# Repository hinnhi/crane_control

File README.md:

# Crane Control

 :building_construction: The following circuit has the purpose of managing three engines controlled by a web app also used as a safety system, 
since upon activation of one of the available motors, If the crane is performing a previously selected operation, 
the operation stops allowing the new selected movement to start. Within the site there are several selectable boxes, such as:
- "Motor 1"; which is associated with the movement of the crane shaft, allowing the rotation to the right or left.
- "Motor 2";  to which is associated the sliding (forward-backward) of the basket along the axis.
- "Motor 3";  which is associated with the climb-down of the basket.
- "Reset"; used to reset the crane axles.

The esp32 connects to a wifi network of which must be provided SSID & PASSWORD and sets the status of the web app to the state "Idle".
Next, if connected to wifi, send requests to the web app and upload the data received in the variable "payload". 
```
int httpCode = http.GET();
if (httpCode > 0){
      payload = http.getString();
      intpayload = payload.toInt();
}
```
The data that can be received, integer type,  can be:
- "1" if Motor 1 has been selected (clockwise spinning)
- "2" if Motor 1 has been selected (counter clockwise spinning)
- "3" if Motor 2 has been selected (clockwise spinning)
- "4" if Motor 2 has been selected (counter clockwise spinning)
- "5" if Motor 3 has been selected (clockwise spinning)
- "6" if Motor 3 has been selected (counter clockwise spinning)
- "7" if selected Reset
  
Depending on the data received, the program will operate the corresponding motor in the corresponding direction.

## Central circuit :space_invader:
[The following circuit](https://github.com/hinnhi/crane_control/tree/main/circuit/circuito_centrale) is responsible for controlling the 3 crane engines. If the relay is not powered 
(so the bistable button, which takes care of stopping all the motors in case of failure/ emergency, has not been pressed) 
the two h bridges are powered by the VCC supply voltage. Once the data is received by the web app, the esp32 sends a 3.3V 
signal output, the signal is sent to a photocoupler and successively to the inputs of the bridge h. The photocouplers are 
used to separate the control part (powered at 3.3V) and that of power (powered by 5V).

## Acoustic and light warning circuit
[The following circuit](https://github.com/hinnhi/crane_control/tree/main/circuit/segnalazione_acustico_luminosa) deals with the acoustic and light signaling of the crane, the LED and the buzzer are operated thanks 
to the use of the integrated circuit [NE555](https://en.wikipedia.org/wiki/555_timer_IC) as a square wave generator. If the relay is powered (so the bistable button, which takes 
care of stopping all the motors in case of failure/ emergency, has been pressed), the integrated NE555 is powered by the VCC 
supply voltage. The circuit also takes care of receiving the VCC supply voltage from the generator and "distribute" it to the 
other circuits, "host" the connectors that connect the limit switches to the espe32 and the bistable button that activates the 
relay. 

## LED blinking circuit
[The following circuit](https://github.com/hinnhi/crane_control/tree/main/circuit/lampeggio_led), realized on millephous base, deals with the light signaling of the crane. The LED flashes thanks to the 
use of the integrated circuit NE555 as a square wave generator. The capacitor C3 is charged with the supply voltage VCC=5V, through the 
two resistors RA and RB; as soon as the power on the capacitor exceeds the level 2/3VCC, the comparator A passes the output Q of the 
flip-flop from low to high, as a result, the T1 transistor goes into saturation and the C3 capacitor begins to discharge through 
the RB resistor. The discharge proceeds until the charge on the capacitor C3 becomes less than 1/3VCC; at this point the comparator 
B makes again change state on the flip-flop bringing the output Q to the low level and the cycle starts again.

Wave period square output:  T = Tc + Ts = (RA+2RB)C3ln(2)

> [!NOTE]
> The power supply voltage can be raised up to 40 volts, but the interfaces for the acoustic and light warning circuit and for the LED blinking circuit must be redesigned.

> [!WARNING]
> Neutral wires of esp32 and power supply must not be connected together.

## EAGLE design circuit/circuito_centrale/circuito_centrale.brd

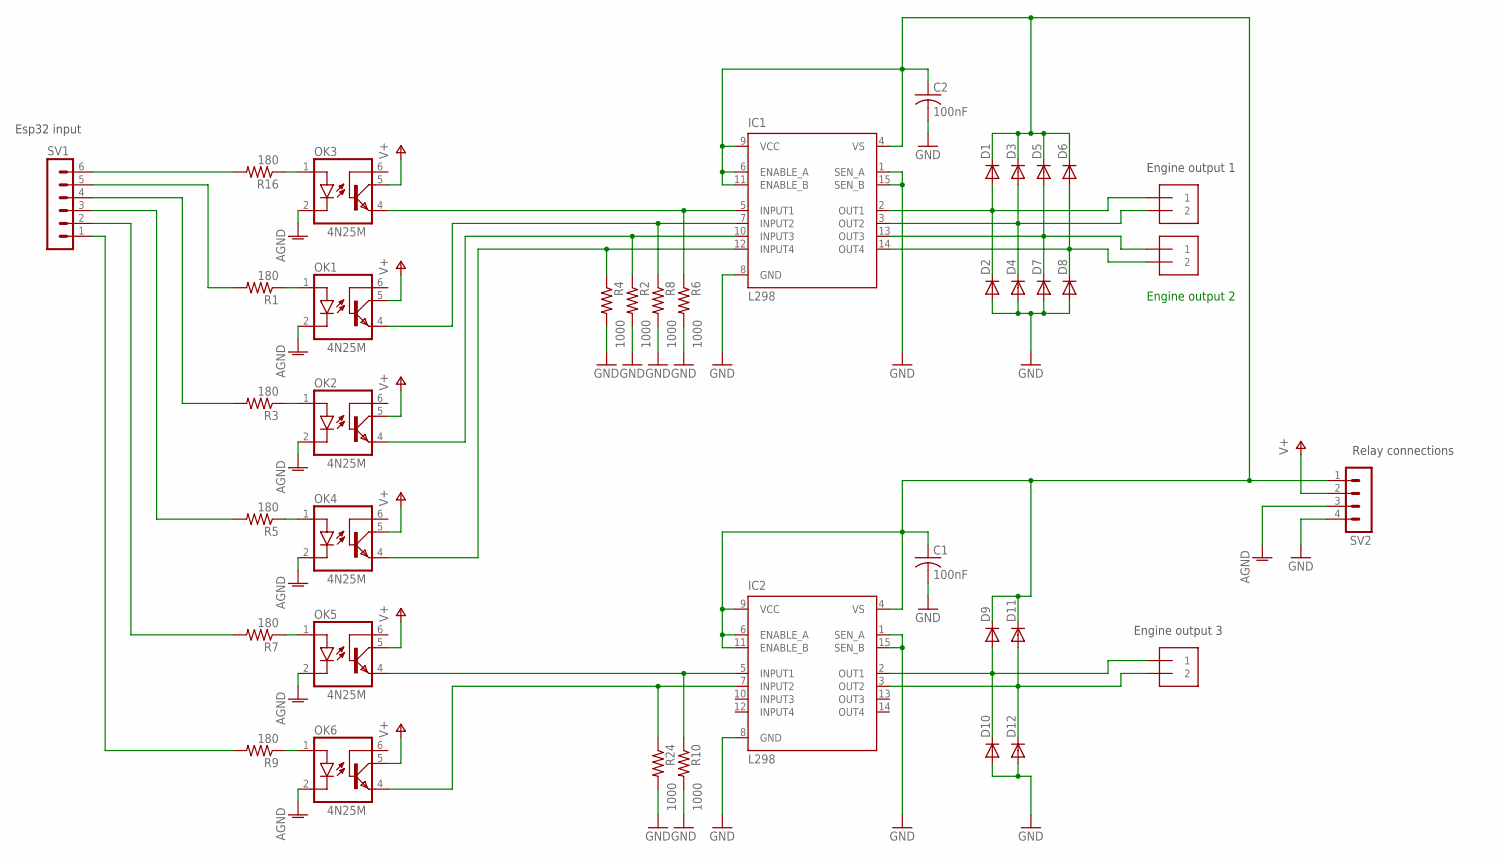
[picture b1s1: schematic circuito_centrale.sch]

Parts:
C1, C2: 100nF; C050-024X044
D1, D2, D3, D4, D5, D6, D7, D8, D9, D10, D11, D12: DIODE-D-5; D-5
IC1, IC2: L298; MULTIWATT-15
J2, J3, J5: 1X2-3.5MM
OK1, OK2, OK3, OK4, OK5, OK6: 4N25M; DIL06
R1, R3, R5, R7, R9, R16: 180; 0207/10
R2, R4, R6, R8, R10, R24: 1000; 0207/10
SV1: MA06-1
SV2: MA04-1

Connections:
AGND: OK1.2 (C), OK2.2 (C), OK3.2 (C), OK4.2 (C), OK5.2 (C), OK6.2 (C), SV2.3
GND: C1.2, C2.2, D2.A, D4.A, D7.A, D8.A, D10.A, D12.A, IC1.1 (SEN_A), IC1.8 (GND), IC1.15 (SEN_B), IC2.1 (SEN_A), IC2.8 (GND), IC2.15 (SEN_B), R2.2, R4.2, R6.2, R8.2, R10.2, R24.2, SV2.4
unnamed: D1.A, D2.C, IC1.2 (OUT1), J2.1
unnamed: D3.A, D4.C, IC1.3 (OUT2), J2.2
unnamed: D6.A, D8.C, IC1.14 (OUT4), J3.2
unnamed: D5.A, D7.C, IC1.13 (OUT3), J3.1
unnamed: IC1.5 (INPUT1), OK3.4 (EMI), R6.1
unnamed: OK1.1 (A), R1.1
unnamed: R1.2, SV1.5
unnamed: IC1.7 (INPUT2), OK1.4 (EMI), R8.1
unnamed: IC1.10 (INPUT3), OK2.4 (EMI), R2.1
unnamed: OK2.1 (A), R3.1
unnamed: R3.2, SV1.4
unnamed: IC1.12 (INPUT4), OK4.4 (EMI), R4.1
unnamed: IC2.5 (INPUT1), OK5.4 (EMI), R10.1
unnamed: OK4.1 (A), R5.1
unnamed: R5.2, SV1.3
unnamed: IC2.7 (INPUT2), OK6.4 (EMI), R24.1
unnamed: D9.A, D10.C, IC2.2 (OUT1), J5.1
unnamed: D11.A, D12.C, IC2.3 (OUT2), J5.2
unnamed: R7.2, SV1.2
unnamed: OK3.1 (A), R16.1
unnamed: R16.2, SV1.6
unnamed: R9.2, SV1.1
unnamed: OK5.1 (A), R7.1
unnamed: OK6.1 (A), R9.1
unnamed: C1.1, C2.1, D1.C, D3.C, D5.C, D6.C, D9.C, D11.C, IC1.4 (VS), IC1.6 (ENABLE_A), IC1.9 (VCC), IC1.11 (ENABLE_B), IC2.4 (VS), IC2.6 (ENABLE_A), IC2.9 (VCC), IC2.11 (ENABLE_B), SV2.1
V+: OK1.5 (COL), OK2.5 (COL), OK3.5 (COL), OK4.5 (COL), OK5.5 (COL), OK6.5 (COL), SV2.2

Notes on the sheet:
Esp32 input
Engine output 1
Engine output 2
Engine output 3
Relay connections

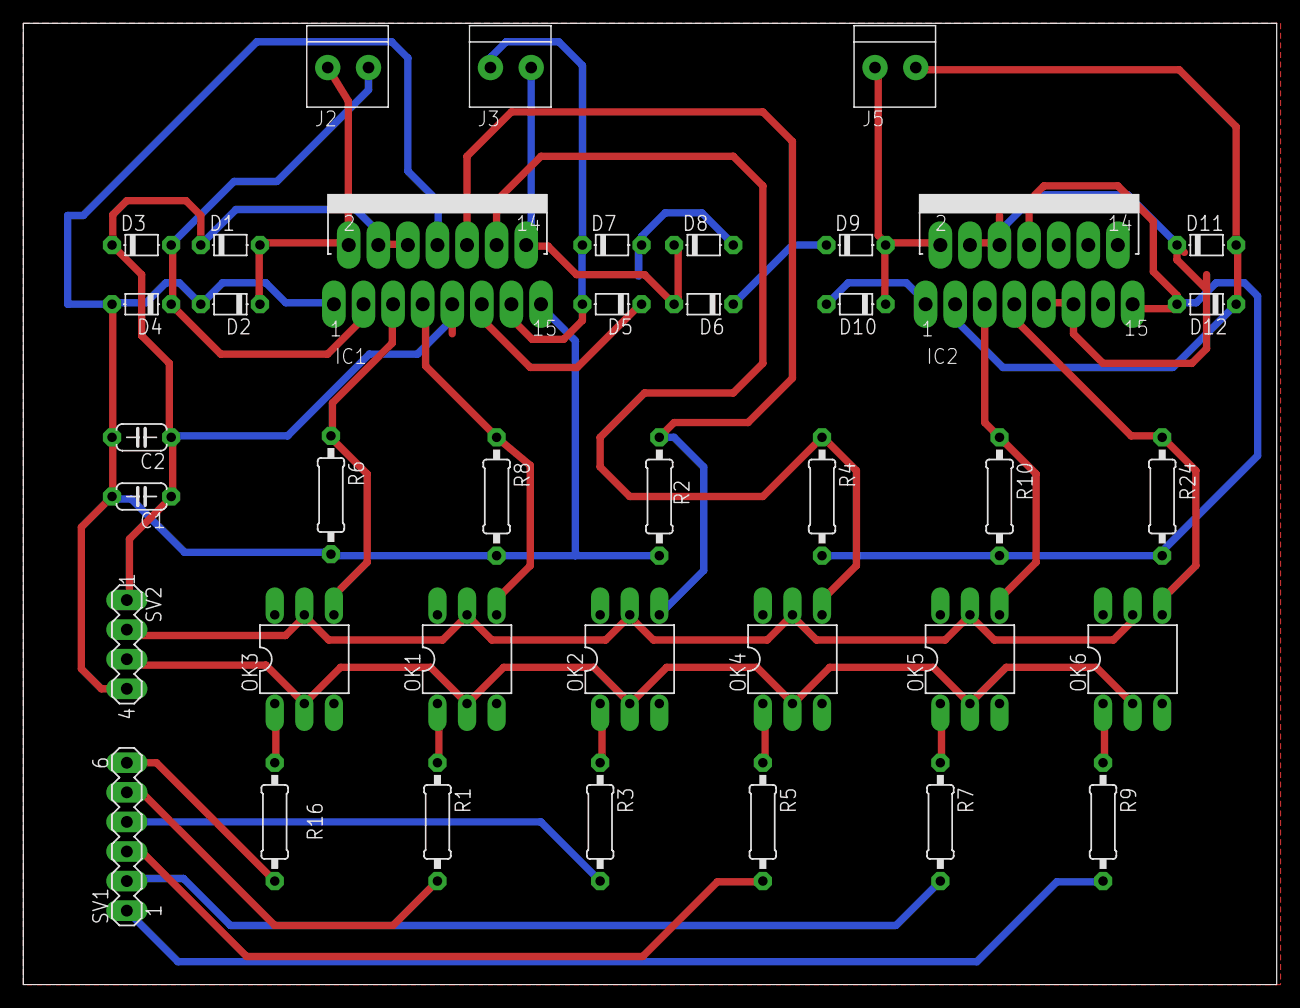
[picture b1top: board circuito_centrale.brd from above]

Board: 2 copper layers, 107.6 x 82.5 mm, 39 parts (0 on the bottom side), 28 nets.

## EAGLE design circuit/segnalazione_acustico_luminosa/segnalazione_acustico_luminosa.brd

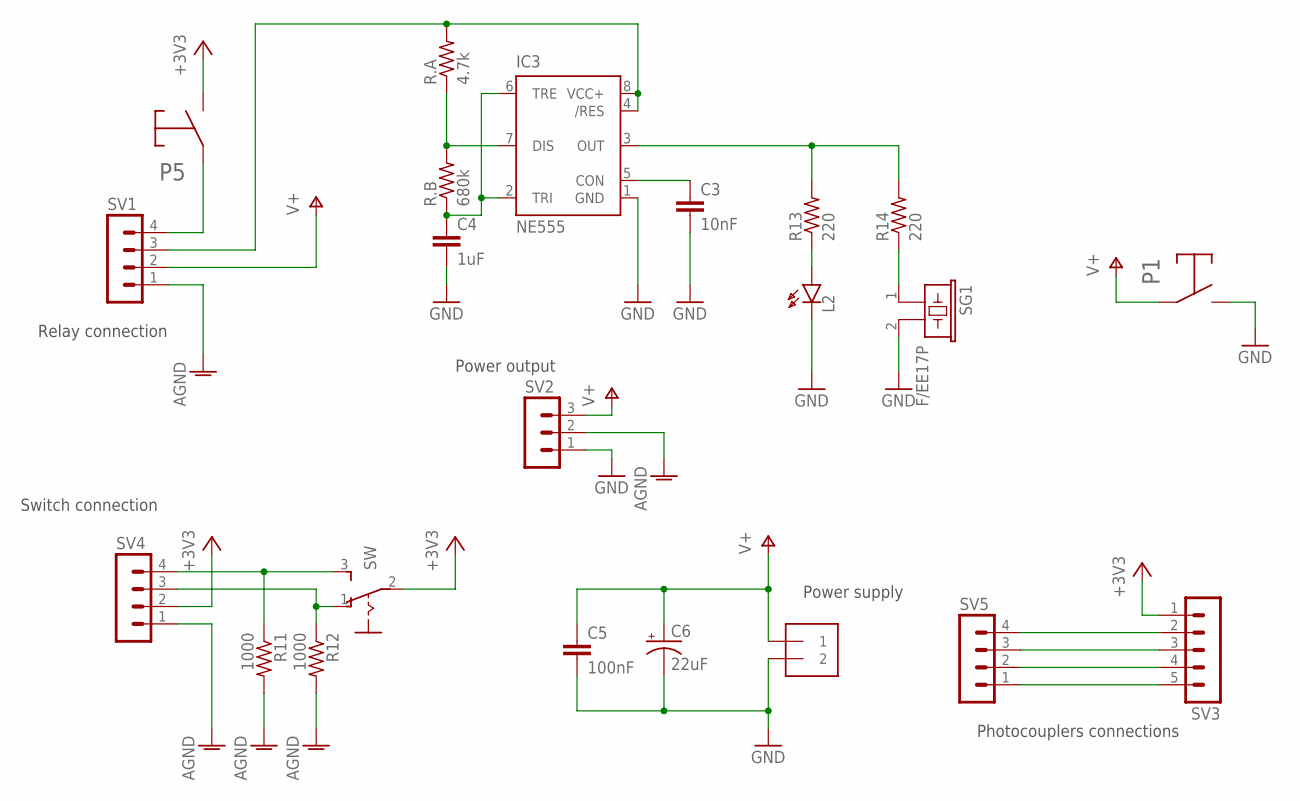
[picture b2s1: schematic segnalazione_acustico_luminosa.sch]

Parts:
C3: 10nF; C025-024X044
C4: 1uF; C025-024X044
C5: 100nF; C025-024X044
C6: 22uF; E2,5-6E
IC3: NE555; DIL-08
J1: 1X2-3.5MM
L2: HLMP6
P1, P5: PULS; 2TULIP
R11, R12: 1000; 0207/10
R13, R14: 220; 0207/10
R.A: 4.7k; 0207/10
R.B: 680k; 0207/10
SG1: F/EE17P
SV1, SV4, SV5: MA04-1
SV2: MA03-1
SV3: MA05-1
SW: M251

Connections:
+3V3: P5.1, SV3.1, SV4.2, SW.2
AGND: R11.2, R12.2, SV1.1, SV2.2, SV4.1
GND: C3.2, C4.2, C5.2, C6.-, IC3.1 (GND), J1.2, L2.K, P1.1, SG1.2, SV2.1
unnamed: IC3.4 (/RES), IC3.8 (VCC+), R.A.2, SV1.3
unnamed: R11.1, SV4.4, SW.3 (S)
unnamed: P5.2, SV1.4
unnamed: R12.1, SV4.3, SW.1 (O)
unnamed: SV3.2, SV5.4
unnamed: SV3.3, SV5.3
unnamed: SV3.4, SV5.2
unnamed: SV3.5, SV5.1
unnamed: R14.1, SG1.1
unnamed: L2.A, R13.1
unnamed: C3.1, IC3.5 (CON)
unnamed: IC3.7 (DIS), R.A.1, R.B.2
unnamed: IC3.3 (OUT), R13.2, R14.2
unnamed: C4.1, IC3.2 (TRI), IC3.6 (TRE), R.B.1
V+: C5.1, C6.+, J1.1, P1.2, SV1.2, SV2.3

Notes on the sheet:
Relay connection
Power output
Switch connection
Power supply
Photocouplers connections

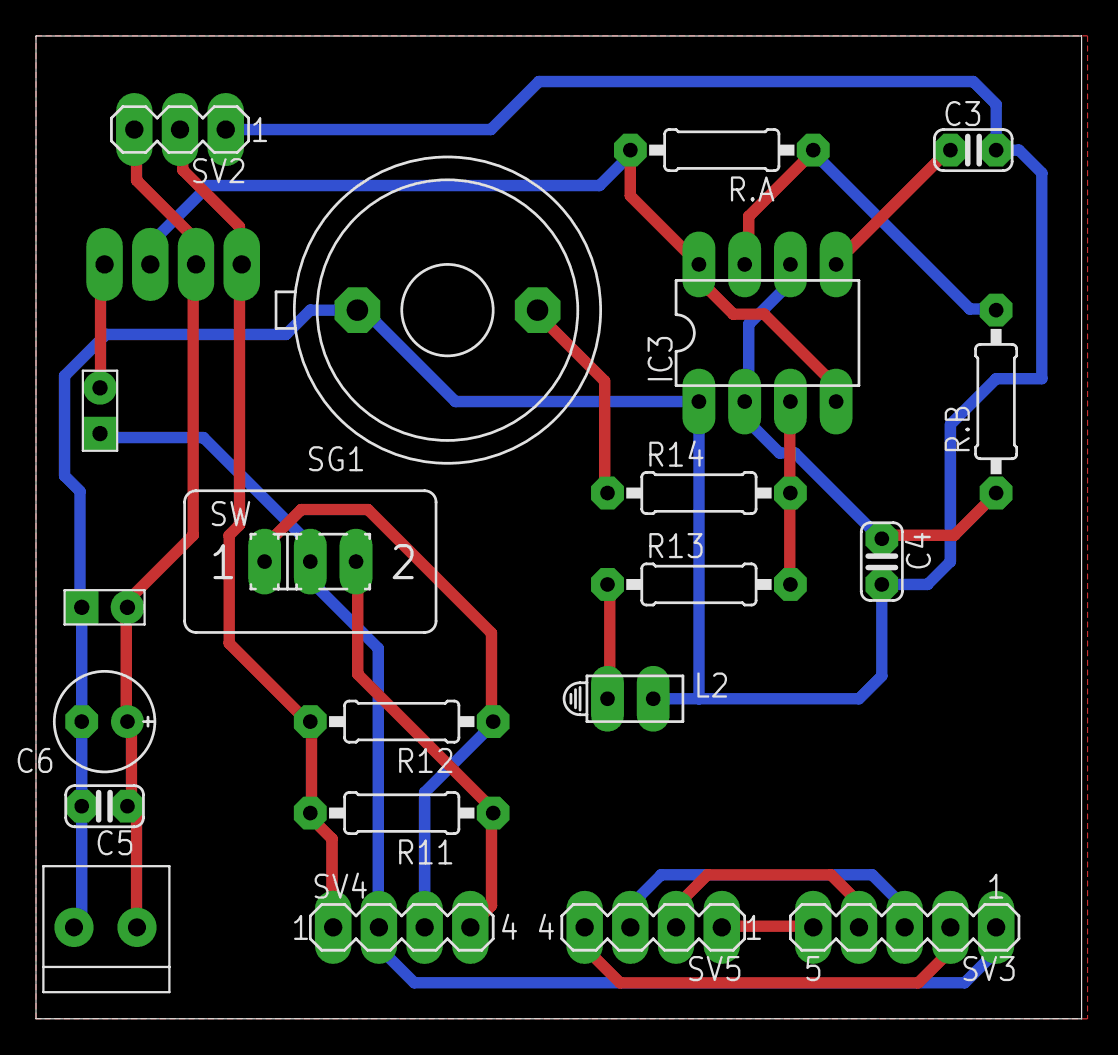
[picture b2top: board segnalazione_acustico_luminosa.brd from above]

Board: 2 copper layers, 58.1 x 54.6 mm, 22 parts (1 on the bottom side), 18 nets.

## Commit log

2024-04-17 init crane server + updated gitignore for node
2024-04-17 frontend + server fixes
2024-04-17 changed fetches urls for deploy
2024-04-25 fix code reset 0 to 7
2024-04-25 fixed Reset Function
2024-04-25 fixed automatic function
